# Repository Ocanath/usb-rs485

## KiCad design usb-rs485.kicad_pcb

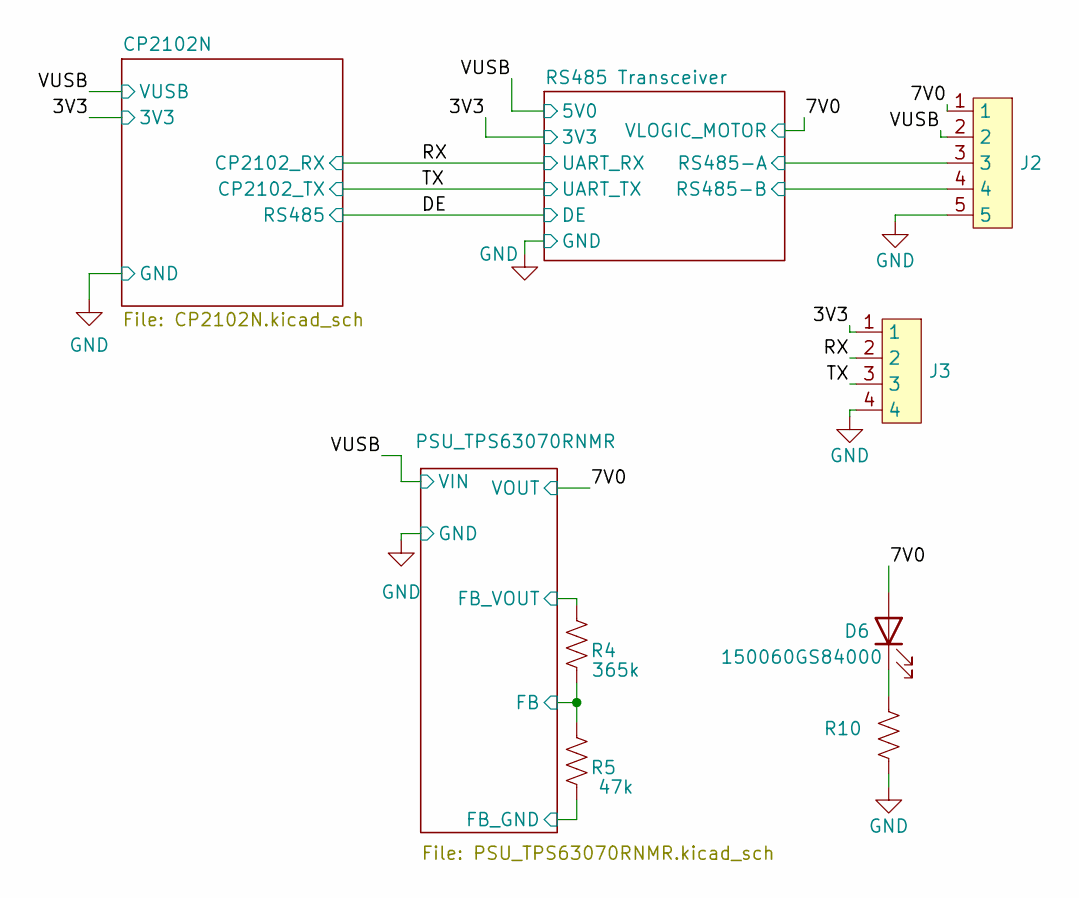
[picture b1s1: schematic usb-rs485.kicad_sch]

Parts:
D6: 150060GS84000; LED_0603_1608Metric
J2: ThruHoleBreadboardX5
J3: ThruHoleBreadboardX4
R4: 365k; R_0402_1005Metric
R5: 47k; R_0402_1005Metric
R10: 470; R_0402_1005Metric

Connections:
+3V3: J3.1; also elsewhere on the board
/7V0: D6.2 (A), J2.1, R4.1; also elsewhere on the board
/PSU_TPS63070RNMR/FB: R4.2, R5.1; also elsewhere on the board
/RS485 Transceiver/RS1_A: J2.3; also elsewhere on the board
/RS485 Transceiver/RS1_B: J2.4; also elsewhere on the board
/RX: J3.2; also elsewhere on the board
/TX: J3.3; also elsewhere on the board
/VUSB: J2.2; also elsewhere on the board
GND: J2.5, J3.4, R5.2, R10.1; also elsewhere on the board
unnamed: D6.1 (K), R10.2

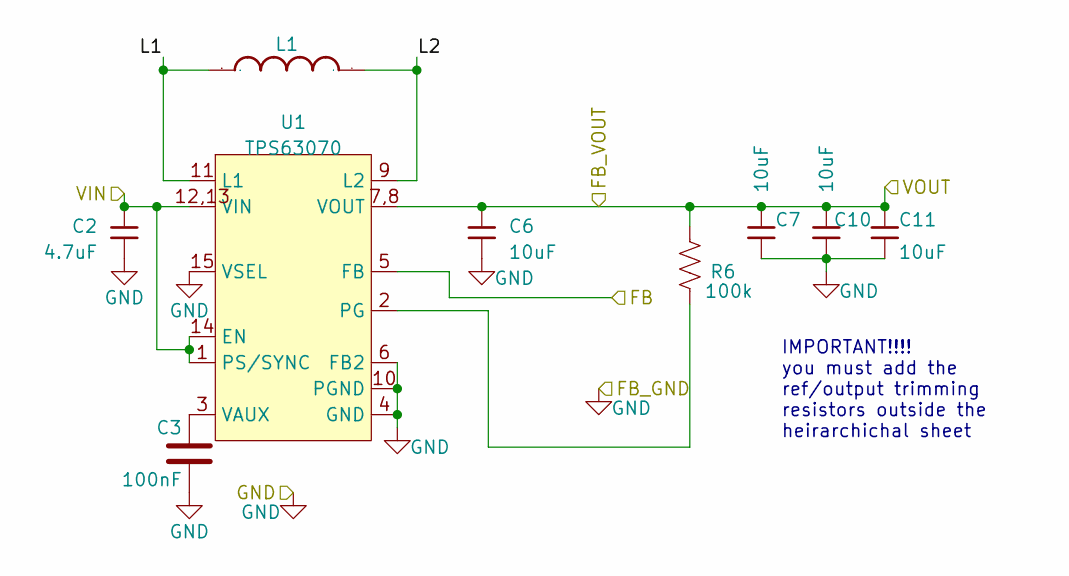
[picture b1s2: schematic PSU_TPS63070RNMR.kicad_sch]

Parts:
C2: 4.7uF; C_0603_1608Metric; Voltage 16V
C3: 100nF; C_0402_1005Metric
C6, C7, C10, C11: 10uF; C_0603_1608Metric
L1: 1277AS-H-1R0M=P2; L_1210_3225Metric
R6: 100k; C_0402_1005Metric
U1: TPS63070; VQFN-TPS63070

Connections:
/7V0: C6.1, C7.1, C10.1, C11.1, R6.1, U1.7,8 (VOUT); also elsewhere on the board
/PSU_TPS63070RNMR/FB: U1.5 (FB); also elsewhere on the board
/PSU_TPS63070RNMR/L1: L1.1, U1.11 (L1)
/PSU_TPS63070RNMR/L2: L1.2, U1.9 (L2)
/VUSB: C2.1, U1.1 (PS/SYNC), U1.12,13 (VIN), U1.14 (EN); also elsewhere on the board
GND: C2.2, C3.2, C6.2, C7.2, C10.2, C11.2, U1.4 (GND), U1.6 (FB2), U1.10 (PGND), U1.15 (VSEL); also elsewhere on the board
unnamed: R6.2, U1.2 (PG)
unnamed: C3.1, U1.3 (VAUX)

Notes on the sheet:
IMPORTANT!!!! you must add the ref/output trimming resistors outside the heirarchichal sheet

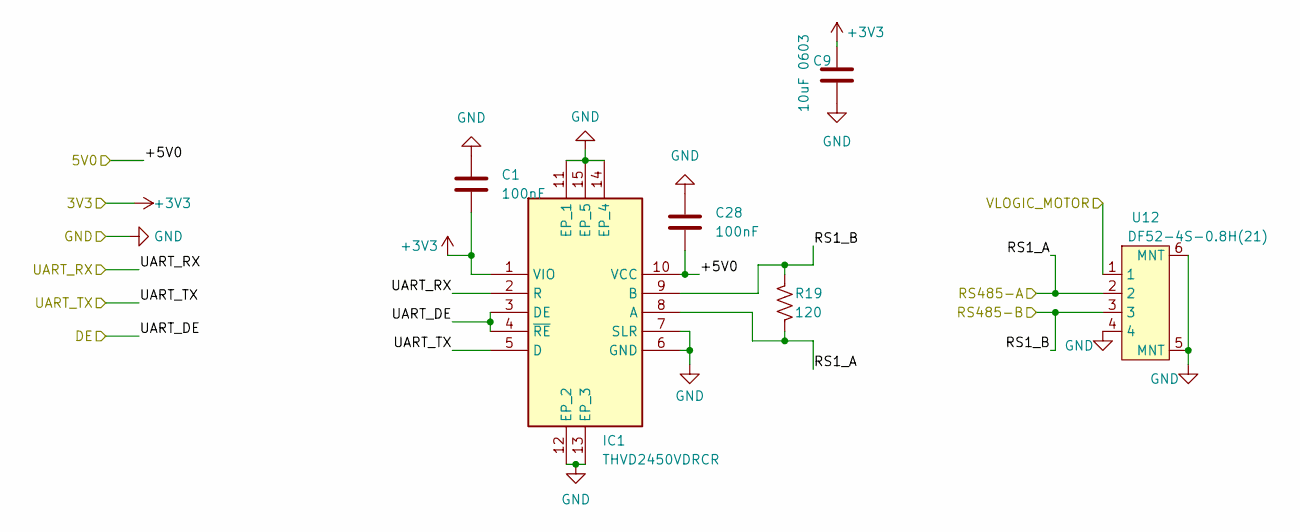
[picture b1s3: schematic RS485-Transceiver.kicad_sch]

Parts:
C1, C28: 100nF; C_0402_1005Metric
C9: 10uF 0603; C_0603_1608Metric; Voltage 10V
IC1: THVD2450VDRCR; THVD2410VDRCR; Manufacturer_Part_Number THVD2450VDRCR; Mouser Part Number 595-THVD2410VDRCR
R19: 120; R_0402_1005Metric
U12: DF52-4S-0.8H(21)

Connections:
+3V3: C1.2, C9.1, IC1.1 (VIO); also elsewhere on the board
/7V0: U12.1; also elsewhere on the board
/DE: IC1.3 (DE), IC1.4 (~RE); also elsewhere on the board
/RS485 Transceiver/RS1_A: IC1.8 (A), R19.1, U12.2; also elsewhere on the board
/RS485 Transceiver/RS1_B: IC1.9 (B), R19.2, U12.3; also elsewhere on the board
/RX: IC1.2 (R); also elsewhere on the board
/TX: IC1.5 (D); also elsewhere on the board
/VUSB: C28.2, IC1.10 (VCC); also elsewhere on the board
GND: C1.1, C9.2, C28.1, IC1.6 (GND), IC1.7 (SLR), IC1.11 (EP_1), IC1.12 (EP_2), IC1.13 (EP_3), IC1.14 (EP_4), IC1.15 (EP_5), U12.4, U12.5 (MNT), U12.6 (MNT); also elsewhere on the board

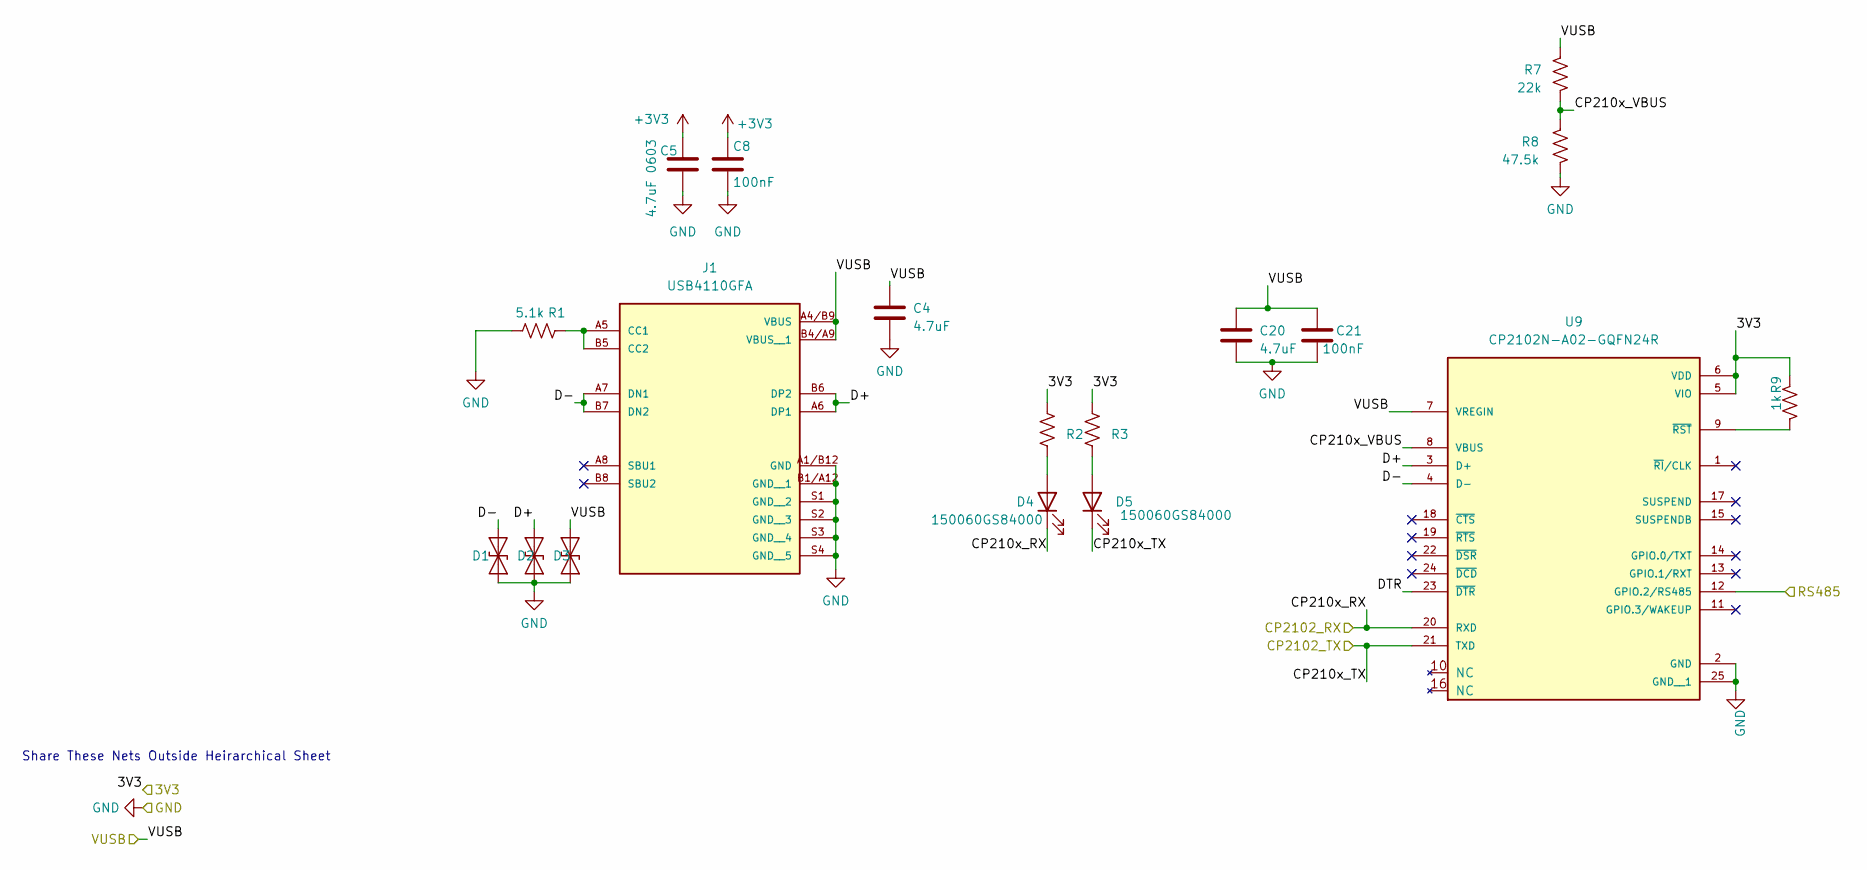
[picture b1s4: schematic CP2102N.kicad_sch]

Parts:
C4, C20: 4.7uF; C_0603_1608Metric
C5: 4.7uF 0603; C_0603_1608Metric; Voltage 10V
C8, C21: 100nF; C_0402_1005Metric
D1, D2, D3: ESD9B3.3ST5G; D_SOD-923
D4, D5: 150060GS84000; LED_0603_1608Metric
J1: USB4110GFA; GCT_USB4110GFA
R1: 5.1k; R_0402_1005Metric
R2, R3: 470; R_0402_1005Metric
R7: 22k; R_0402_1005Metric
R8: 47.5k; R_0402_1005Metric
R9: 1k; R_0402_1005Metric
U9: CP2102N-A02-GQFN24R; QFN50P400X400X80-25N; PARTREV 1.3

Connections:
+3V3: C5.1, C8.1, R2.1, R3.1, R9.2, U9.5 (VIO), U9.6 (VDD); also elsewhere on the board
/CP2102N/CP210x_VBUS: R7.1, R8.2, U9.8 (VBUS)
/CP2102N/D+: D2.2 (A2), J1.A6 (DP1), J1.B6 (DP2), U9.3 (D+)
/CP2102N/D-: D1.2 (A2), J1.A7 (DN1), J1.B7 (DN2), U9.4 (D-)
/CP2102N/DTR: U9.23 (~DTR)
/DE: U9.12 (GPIO.2/RS485); also elsewhere on the board
/RX: D4.1 (K), U9.20 (RXD); also elsewhere on the board
/TX: D5.1 (K), U9.21 (TXD); also elsewhere on the board
/VUSB: C4.1, C20.1, C21.1, D3.2 (A2), J1.A4/B9 (VBUS), J1.B4/A9 (VBUS__1), R7.2, U9.7 (VREGIN); also elsewhere on the board
GND: C4.2, C5.2, C8.2, C20.2, C21.2, D1.1 (A1), D2.1 (A1), D3.1 (A1), J1.A1/B12 (GND), J1.B1/A12 (GND__1), J1.S1 (GND__2), J1.S2 (GND__3), J1.S3 (GND__4), J1.S4 (GND__5), R1.1, R8.1, U9.2 (GND), U9.25 (GND__1); also elsewhere on the board
unnamed: D4.2 (A), R2.2
unnamed: D5.2 (A), R3.2
unnamed: J1.A5 (CC1), J1.B5 (CC2), R1.2
unnamed: R9.1, U9.9 (~RST)

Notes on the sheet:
Share These Nets Outside Heirarchical Sheet

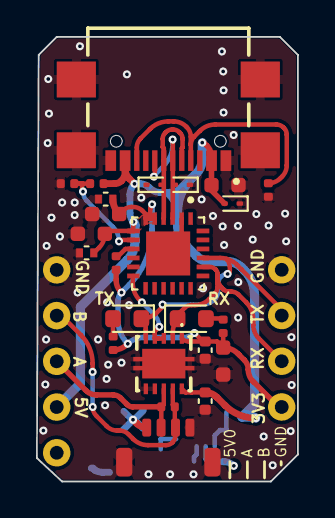
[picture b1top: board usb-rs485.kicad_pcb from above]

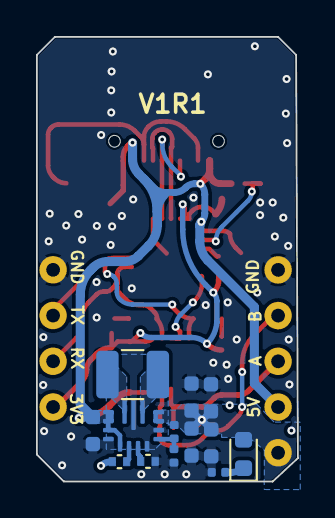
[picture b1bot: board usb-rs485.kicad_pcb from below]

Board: 4 copper layers, 14.5 x 24.7 mm, 39 parts (13 on the bottom side), 22 nets.

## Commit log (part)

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2026-05-25 init comit tore up the coprocessor
2026-05-25 gitignore, datasheet for cp2102n added
2026-05-25 backups removalled schematic looking correct if not good
2026-05-25 library table
2026-05-25 cleanup some routing
2026-05-25 routing
2026-05-25 routed, thru holes. ready to order i think
2026-05-25 removed inner 2 and made it wavyy
2026-05-25 rename library to be for this
2026-05-25 starting to add power
2026-05-25 wiring in boost to 6V
2026-05-25 moved it elsewhere but MEH
2026-05-25 routed best placement. Has 6V on the output and on a final header hole for max conveniences
2026-05-25 resistors dialed in
2026-05-25 tweaks to layouts
2026-05-25 lights
2026-06-03 bom callouts no copper change
